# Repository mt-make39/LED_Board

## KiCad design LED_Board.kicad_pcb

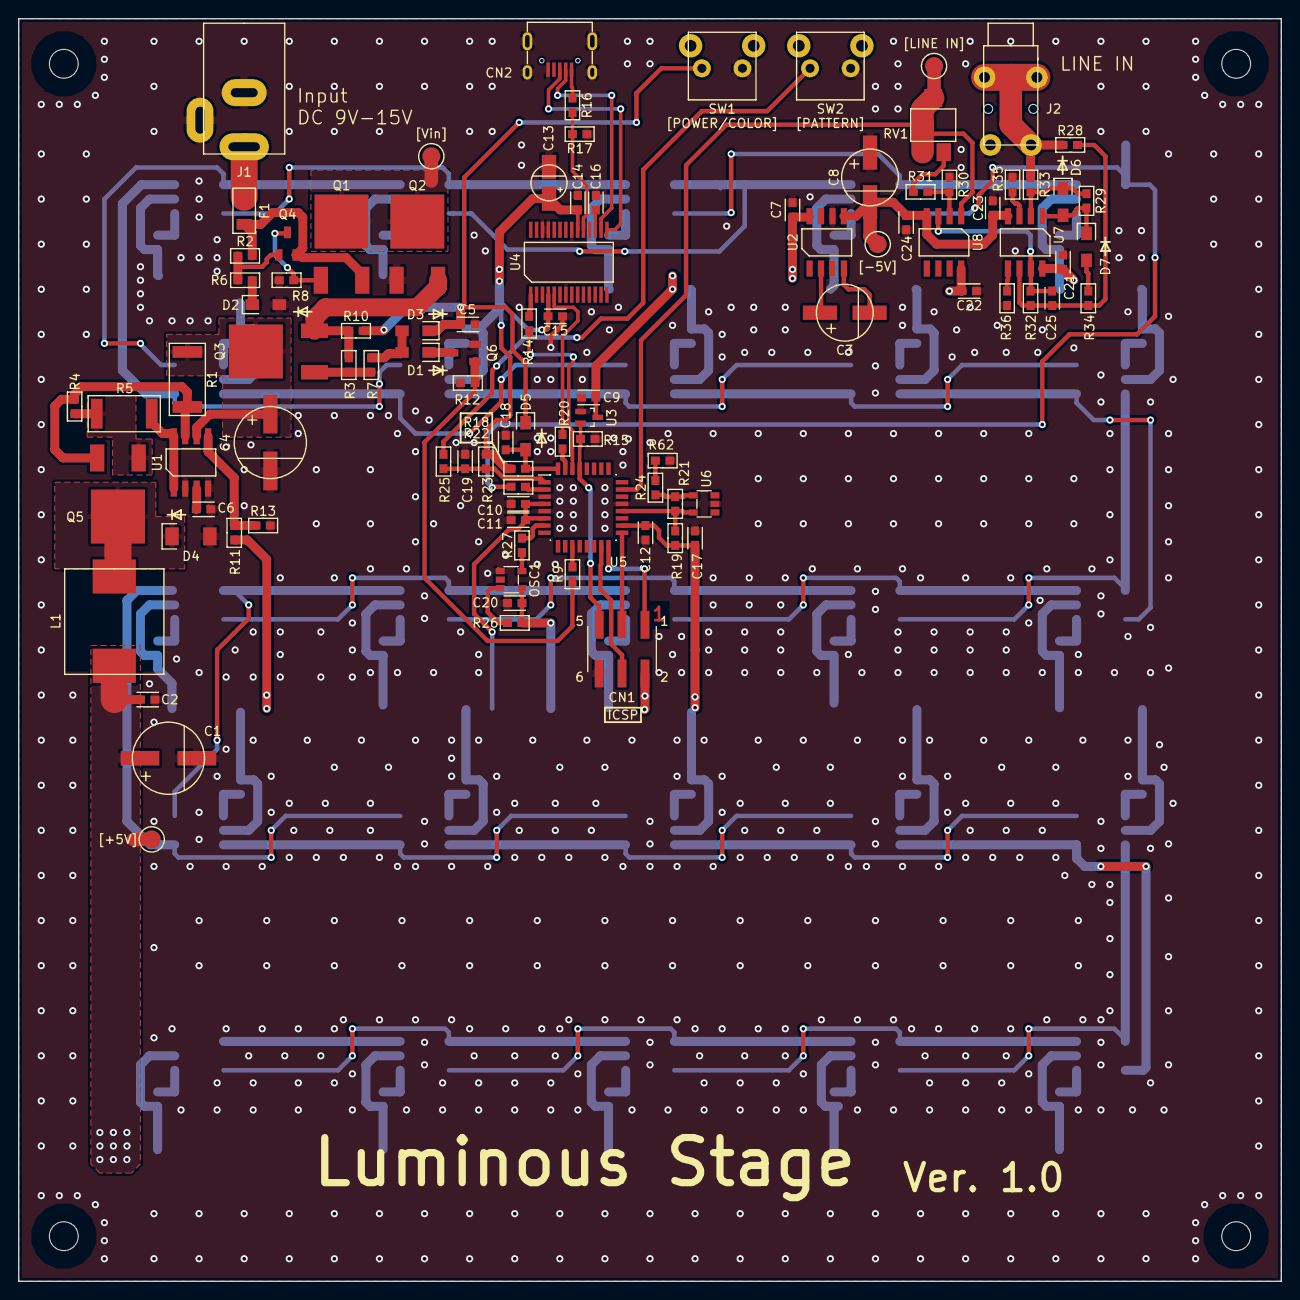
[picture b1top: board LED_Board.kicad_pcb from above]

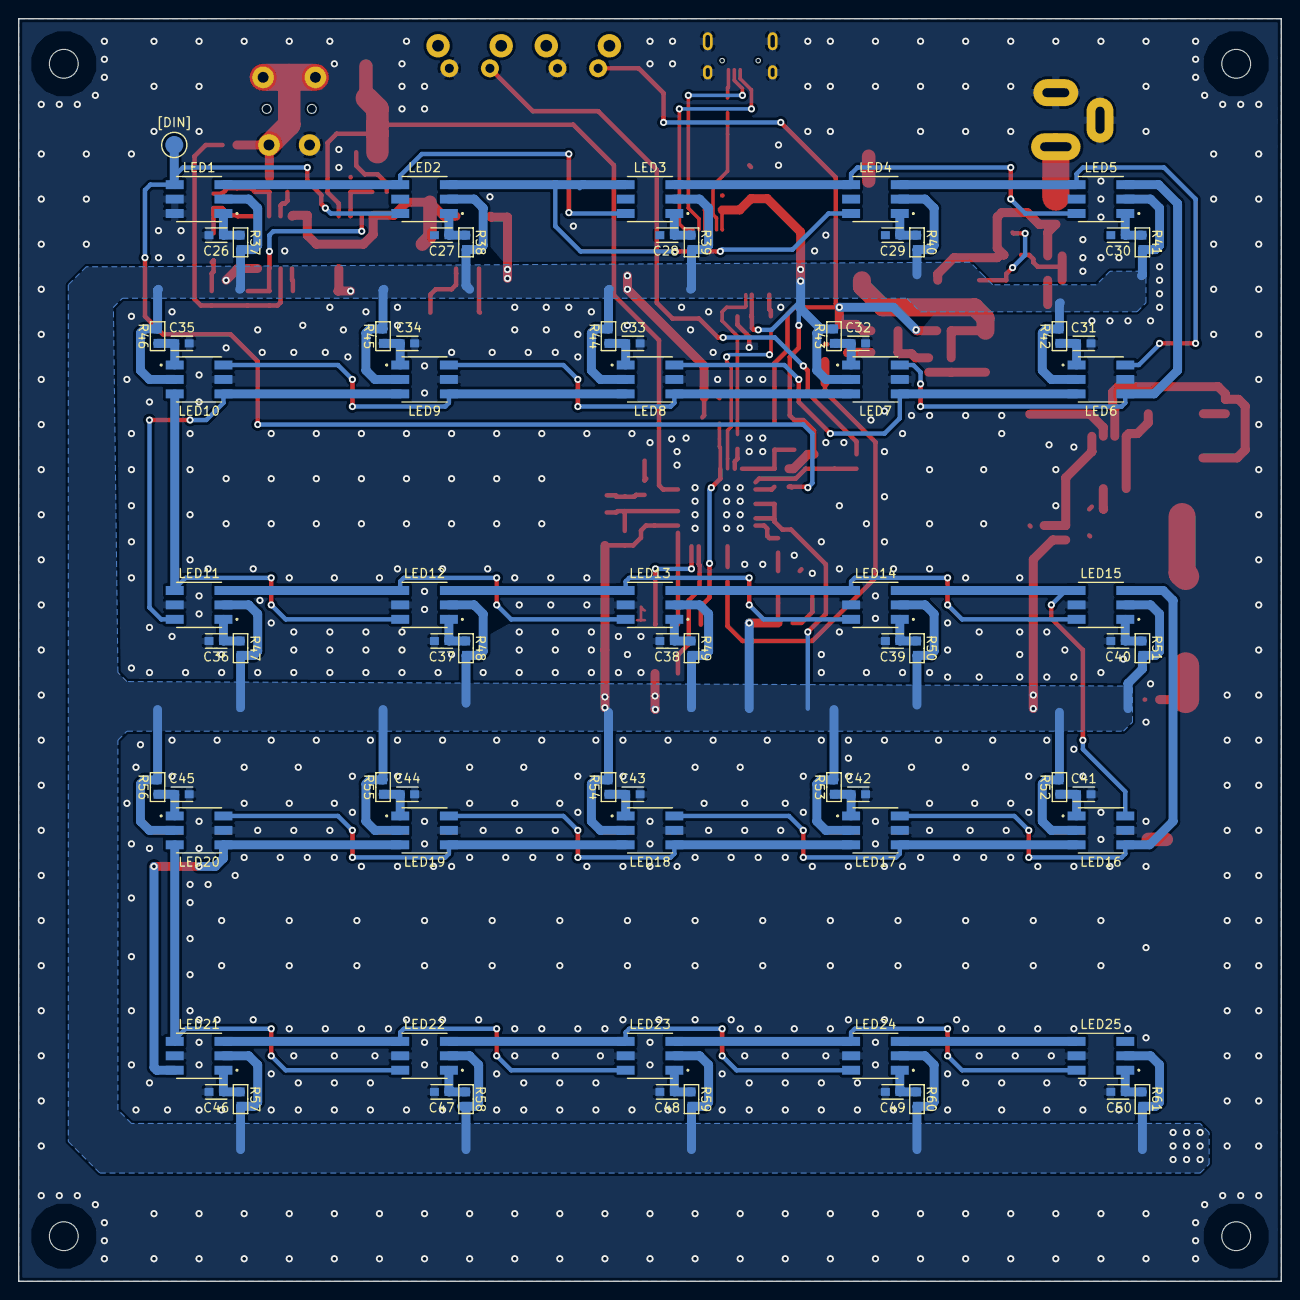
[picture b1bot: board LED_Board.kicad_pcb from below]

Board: 2 copper layers, 140.0 x 140.0 mm, 168 parts (75 on the bottom side), 109 nets.

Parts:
C1, C4: 470u; Φ8mm
C2, C5, C7, C9, C10, C11, C12, C14, C15, C16, C17, C18, C19, C20, C21, C22, C23, C24, C26, C27, C28, C29, C30, C31, C32, C33, C34, C35, C36, C37, C38, C39, C40, C41, C42, C43, C44, C45, C46, C47, C48, C49, C50: 0.1u; C_1608
C3, C8: 220u; Φ6.3mm
C6: 330p; C_1608
C13: 4.7u; Φ4mm
C25: 470p; C_1608
CN1: AVR-ISP-6; 2×3(6pin)_SMD
CN2: microUSB; microUSB(U-F-M5DD-W-2)
D1, D3, D5, D6, D7: D; SOD-123FL
D2: D_Zener; SOD-123FL
D4: D; SOD-128
F1: F_Small; R_3216
J1: BARREL_JACK; MJ-179PH
J2: 3.5mm_stereo_mini_ST_005_G; STEREO_MINI_35
L1: 33u 5A; ETQ-P5MxxxYFC
LED1, LED2, LED3, LED4, LED5, LED6, LED7, LED8, LED9, LED10, LED11, LED12, LED13, LED14, LED15, LED16, LED17, LED18, LED19, LED20, LED21, LED22, LED23, LED24, LED25: WS2813
OSC1: SIT2001B; SOT-23-5(MTP5)
Q1, Q2, Q3: Q_PMOS_GDS; D-PAK(SC-63)
Q4: Q_PNP_BEC; TO-236MOD(SC-59)
Q5: Q_PNP_BCE; D-PAK(SC-63)
Q6: Q_NPN_BEC; TO-236MOD(SC-59)
R1: 0.05; R_6432
R2: 680; R_1608
R3, R19, R30, R31: 2.2k; R_1608
R4: 150; R_1608
R5: 330; R_6432
R6: 6.2k; R_1608
R7, R9, R12, R17, R18, R23, R26, R29, R33, R34: 10k; R_1608
R8: 15k; R_1608
R10: 47k; R_1608
R11: 33k; R_1608
R13: 11k; R_1608
R14, R20, R22, R27: 22; R_1608
R15: 100k; R_1608
R16, R35, R36: 4.7k; R_1608
R21: 120k; R_1608
R24: 130k; R_1608
R25: 100; R_1608
R28, R32: 20k; R_1608
R37, R38, R39, R40, R41, R42, R43, R44, R45, R46, R47, R48, R49, R50, R51, R52, R53, R54, R55, R56, R57, R58, R59, R60, R61: 220; R_1608
R62: 1k; R_1608
RV1: 100k; ST-4EB
SW1, SW2: SW_PUSH; SKHHLPA010
U1: NJM2360; SOP-8pin
U2: MAX660; SOP-8pin
U3: TCM809; SC-70
U4: FT232RL; SSOP_28pin
U5: ATMEGA328P-A; QFP_0.8_32pin
U6: NJM2825; SOT-23-5(MTP5)
U7, U8: NJM072; SOP-8pin

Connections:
+5V: C1.1, C2.1, C7.1, C9.1, C10.1, C11.1, C12.1, C13.1, C14.1, C15.1, C17.1, C20.1, C21.1, C22.1, CN1.2, L1.2, LED1.2, LED2.2, LED3.2, LED4.2, LED5.2, LED6.2, LED7.2, LED8.2, LED9.2, LED10.2, LED11.2, LED12.2, LED13.2, LED14.2, LED15.2, LED16.2, LED17.2, LED18.2, LED19.2, LED20.2, LED21.2, LED22.2, LED23.2, LED24.2, LED25.2, OSC1.4, R11.2, R18.1, R19.2, R23.1, R26.1, R37.1, R38.1, R39.1, R40.1, R41.1, R42.1, R43.1, R44.1, R45.1, R46.1, R47.1, R48.1, R49.1, R50.1, R51.1, R52.1, R53.1, R54.1, R55.1, R56.1, R57.1, R58.1, R59.1, R60.1, R61.1, U2.8, U3.3, U4.4, U4.20, U5.4, U5.6, U5.18, U7.8, U8.8
-5V: C8.2, C23.2, C24.2, U2.5, U7.4, U8.4
/LED/DIN: LED1.4, LED2.6, R22.1
GND: C1.2, C2.2, C4.2, C5.2, C6.2, C7.2, C8.1, C9.2, C10.2, C11.2, C12.2, C13.2, C14.2, C15.2, C16.2, C17.2, C18.2, C19.2, C20.2, C21.2, C22.2, C23.1, C24.1, C26.2, C31.2, C32.2, C33.2, C34.2, C35.2, C36.2, C37.2, C38.2, C39.2, C40.2, C41.2, C42.2, C43.2, C44.2, C45.2, C46.2, C47.2, C48.2, C49.2, C50.2, CN1.6, CN2.5, CN2.6, D2.2, D4.2, J1.2, J1.3, J2.3, LED1.5, LED1.6, LED6.5, LED7.5, LED8.5, LED9.5, LED10.5, LED11.5, LED12.5, LED13.5, LED14.5, LED15.5, LED16.5, LED17.5, LED18.5, LED19.5, LED20.5, LED21.5, LED22.5, LED23.5, LED24.5, LED25.5, OSC1.1, Q2.1, Q6.2, R8.2, R12.2, R13.1, R15.2, R17.2, R30.2, R35.1, R36.1, R62.2, SW1.1, SW2.1, U1.2, U1.4, U2.3, U2.6, U3.1, U4.7, U4.18, U4.21, U4.25, U4.26, U5.3, U5.5, U5.21, U6.2
unnamed: C3.1, U2.2
unnamed: C3.2, U2.4
unnamed: C4.1, Q3.2, R1.2, U1.6
unnamed: C6.1, U1.3
unnamed: C16.1, U4.17
unnamed: C18.1, D5.2, R18.2, U5.32
unnamed: C19.1, R23.2, R25.1, U5.1
unnamed: C25.1, R32.1, U7.7, U8.3
unnamed: C25.2, R28.1, R32.2, R34.1, U7.6
unnamed: C26.1, LED1.1, R37.2
unnamed: C27.1, LED2.1, R38.2
unnamed: C28.1, LED3.1, R39.2
unnamed: C29.1, LED4.1, R40.2
unnamed: C30.1, LED5.1, R41.2
unnamed: C31.1, LED6.1, R42.2
unnamed: C32.1, LED7.1, R43.2
unnamed: C33.1, LED8.1, R44.2
unnamed: C34.1, LED9.1, R45.2
unnamed: C35.1, LED10.1, R46.2
unnamed: C36.1, LED11.1, R47.2
unnamed: C37.1, LED12.1, R48.2
unnamed: C38.1, LED13.1, R49.2
unnamed: C39.1, LED14.1, R50.2
unnamed: C40.1, LED15.1, R51.2
unnamed: C41.1, LED16.1, R52.2
unnamed: C42.1, LED17.1, R53.2
unnamed: C43.1, LED18.1, R54.2
unnamed: C44.1, LED19.1, R55.2
unnamed: C45.1, LED20.1, R56.2
unnamed: C46.1, LED21.1, R57.2
unnamed: C47.1, LED22.1, R58.2
unnamed: C48.1, LED23.1, R59.2
unnamed: C49.1, LED24.1, R60.2
unnamed: C50.1, LED25.1, R61.2
unnamed: CN1.1, U5.16
unnamed: CN1.3, U5.17
unnamed: CN1.4, U5.15
unnamed: CN1.5, R15.1, U3.2, U5.29
unnamed: CN2.1, R16.2
unnamed: CN2.2, U4.16
unnamed: CN2.3, U4.15
unnamed: D1.1, Q6.3
unnamed: D1.2, D3.2, R7.2
unnamed: D2.1, R6.2
unnamed: D4.1, L1.1, Q5.2
unnamed: D6.1, R29.2, R33.1, U7.2
unnamed: D6.2, D7.1, R29.1, U7.1
unnamed: D7.2, R34.2
unnamed: F1.1, J1.1
unnamed: F1.2, Q1.3, Q4.2, R2.1
unnamed: J2.2, J2.4, R28.2, R33.2
unnamed: LED1.3, LED2.4, LED3.6
unnamed: LED2.3, LED3.4, LED4.6
unnamed: LED3.3, LED4.4, LED5.6
unnamed: LED4.3, LED5.4, LED6.6
unnamed: LED5.3, LED6.4, LED7.6
unnamed: LED6.3, LED7.4, LED8.6
unnamed: LED7.3, LED8.4, LED9.6
unnamed: LED10.3, LED11.4, LED12.6
unnamed: LED9.3, LED10.4, LED11.6
unnamed: LED8.3, LED9.4, LED10.6
unnamed: LED11.3, LED12.4, LED13.6
unnamed: LED12.3, LED13.4, LED14.6
unnamed: LED13.3, LED14.4, LED15.6
unnamed: LED14.3, LED15.4, LED16.6
unnamed: LED15.3, LED16.4, LED17.6
unnamed: LED16.3, LED17.4, LED18.6
unnamed: LED17.3, LED18.4, LED19.6
unnamed: LED18.3, LED19.4, LED20.6
unnamed: LED19.3, LED20.4, LED21.6
unnamed: LED20.3, LED21.4, LED22.6
unnamed: LED21.3, LED22.4, LED23.6
unnamed: LED22.3, LED23.4, LED24.6
unnamed: LED23.3, LED24.4, LED25.6
unnamed: LED24.3, LED25.4
unnamed: OSC1.3, R26.2
unnamed: OSC1.5, R27.2
unnamed: Q1.1, Q4.3, R8.1
unnamed: Q1.2, Q2.2
unnamed: Q2.3, Q3.3, R3.1, R10.1
unnamed: Q3.1, R3.2, R7.1
unnamed: Q4.1, R2.2, R6.1
unnamed: Q5.1, R4.1, R5.1
unnamed: Q5.3, R1.1, R4.2, U1.7
unnamed: Q6.1, R9.2, R12.1
unnamed: R5.2, U1.1, U1.8
unnamed: R11.1, R13.2, U1.5
unnamed: R14.1, U5.30
unnamed: R14.2, U4.1
unnamed: R16.1, R17.1, U4.19
unnamed: R19.1, R21.1, U5.20, U6.5
unnamed: R20.1, U4.5
unnamed: R20.2, U5.31
unnamed: R21.2, R24.1, U6.4
unnamed: R22.2, U5.2
unnamed: R24.2, R62.1
unnamed: R25.2, SW2.2
unnamed: R27.1, U5.7
unnamed: R30.1, R31.2, U8.2
unnamed: R31.1, RV1.1
unnamed: R35.2, U7.3
unnamed: R36.2, U7.5
unnamed: RV1.2, RV1.3, U5.23, U8.1
PWR_ON: R9.1, U5.11
PWR_SW: C5.1, D3.1, D5.1, R10.2, SW1.2

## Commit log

2019-01-29 Add New
